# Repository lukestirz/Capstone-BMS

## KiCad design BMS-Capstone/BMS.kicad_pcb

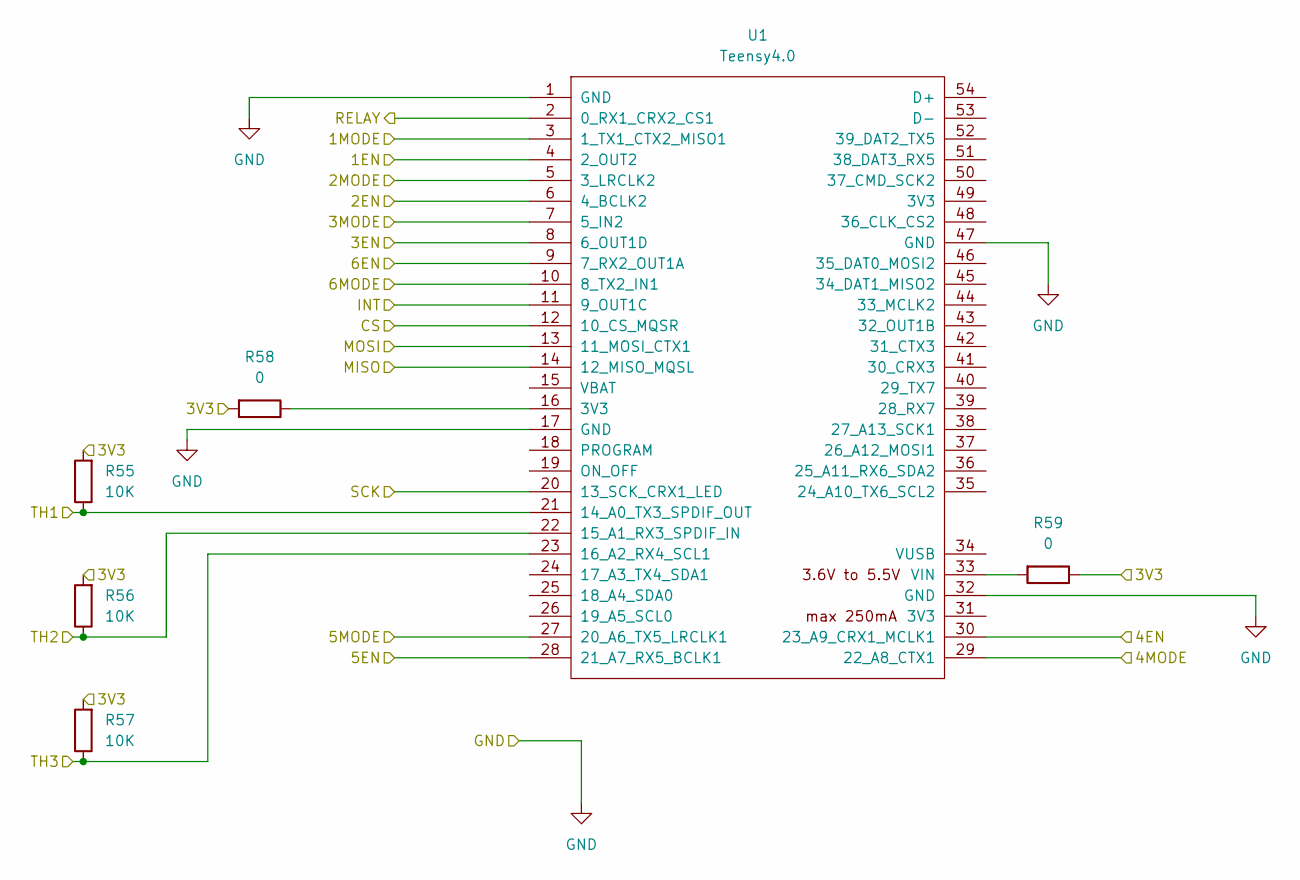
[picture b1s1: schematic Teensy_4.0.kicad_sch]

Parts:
R55, R56, R57: 10K; R_0805_2012Metric
R58, R59: 0; R_0805_2012Metric
U1: Teensy4.0; Teensy40_SMT

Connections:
/BMS Board/1EN: U1.4 (2_OUT2); also elsewhere on the board
/BMS Board/1MODE: U1.3 (1_TX1_CTX2_MISO1); also elsewhere on the board
/BMS Board/2EN: U1.6 (4_BCLK2); also elsewhere on the board
/BMS Board/2MODE: U1.5 (3_LRCLK2); also elsewhere on the board
/BMS Board/3EN: U1.8 (6_OUT1D); also elsewhere on the board
/BMS Board/3MODE: U1.7 (5_IN2); also elsewhere on the board
/BMS Board/4EN: U1.30 (23_A9_CRX1_MCLK1); also elsewhere on the board
/BMS Board/4MODE: U1.29 (22_A8_CTX1); also elsewhere on the board
/BMS Board/5EN: U1.28 (21_A7_RX5_BCLK1); also elsewhere on the board
/BMS Board/5MODE: U1.27 (20_A6_TX5_LRCLK1); also elsewhere on the board
/BMS Board/6EN: U1.9 (7_RX2_OUT1A); also elsewhere on the board
/BMS Board/6MODE: U1.10 (8_TX2_IN1); also elsewhere on the board
/BMS Board/RELAY: U1.2 (0_RX1_CRX2_CS1); also elsewhere on the board
/BMS Board/TH1: R55.1, U1.21 (14_A0_TX3_SPDIF_OUT); also elsewhere on the board
/BMS Board/TH2: R56.1, U1.22 (15_A1_RX3_SPDIF_IN); also elsewhere on the board
/BMS Board/TH3: R57.1, U1.23 (16_A2_RX4_SCL1); also elsewhere on the board
/Monitoring/3.3V: R55.2, R56.2, R57.2, R58.2, R59.1; also elsewhere on the board
/Monitoring/INT: U1.11 (9_OUT1C); also elsewhere on the board
/Monitoring/SPI_CS: U1.12 (10_CS_MQSR); also elsewhere on the board
/Monitoring/SPI_MISO: U1.14 (12_MISO_MQSL); also elsewhere on the board
/Monitoring/SPI_MOSI: U1.13 (11_MOSI_CTX1); also elsewhere on the board
/Monitoring/SPI_SCLK: U1.20 (13_SCK_CRX1_LED); also elsewhere on the board
GND: U1.1 (GND), U1.17 (GND), U1.32 (GND), U1.47 (GND); also elsewhere on the board
unnamed: R58.1, U1.16 (3V3)
unnamed: R59.2, U1.33 (VIN)

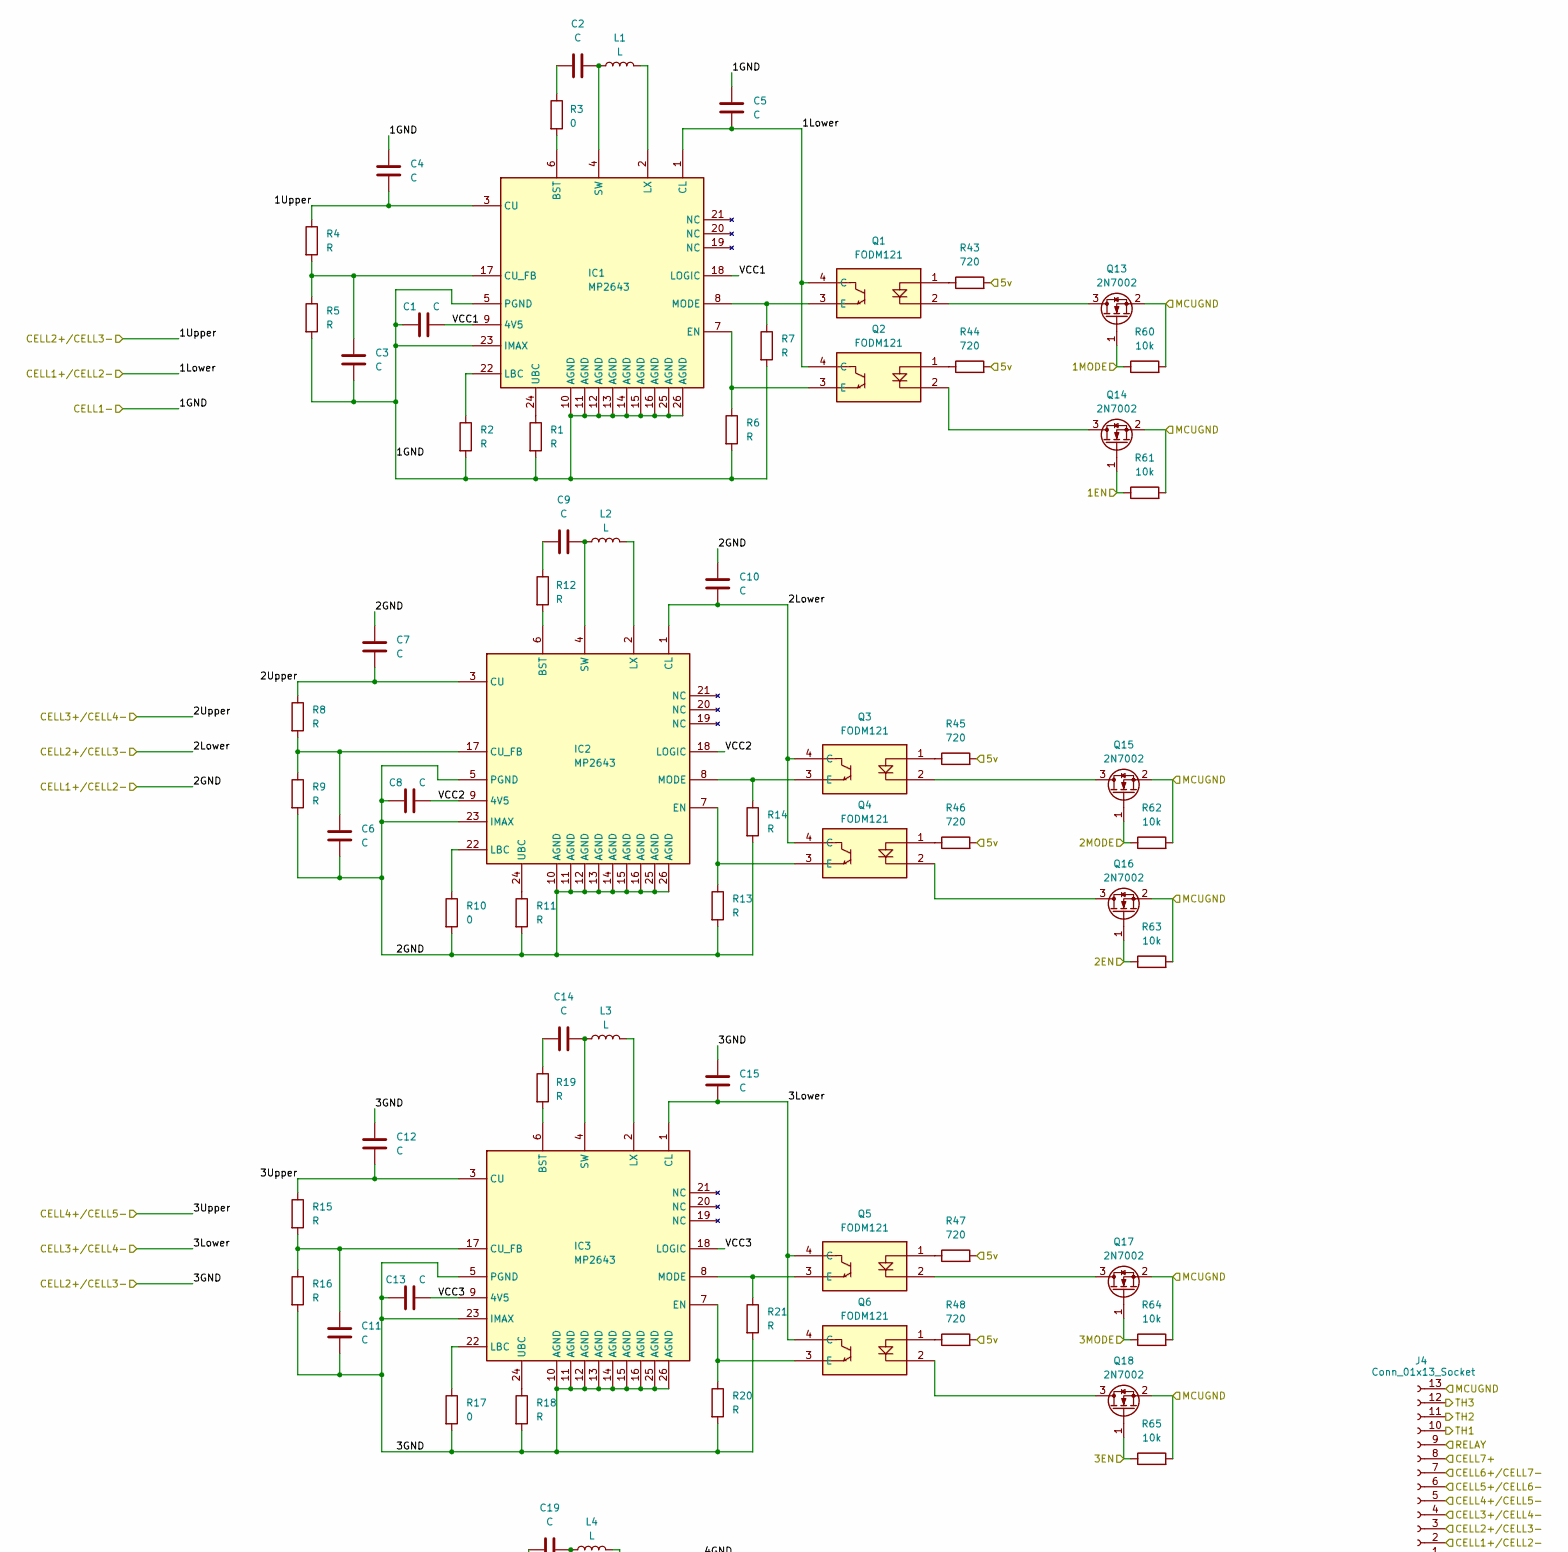
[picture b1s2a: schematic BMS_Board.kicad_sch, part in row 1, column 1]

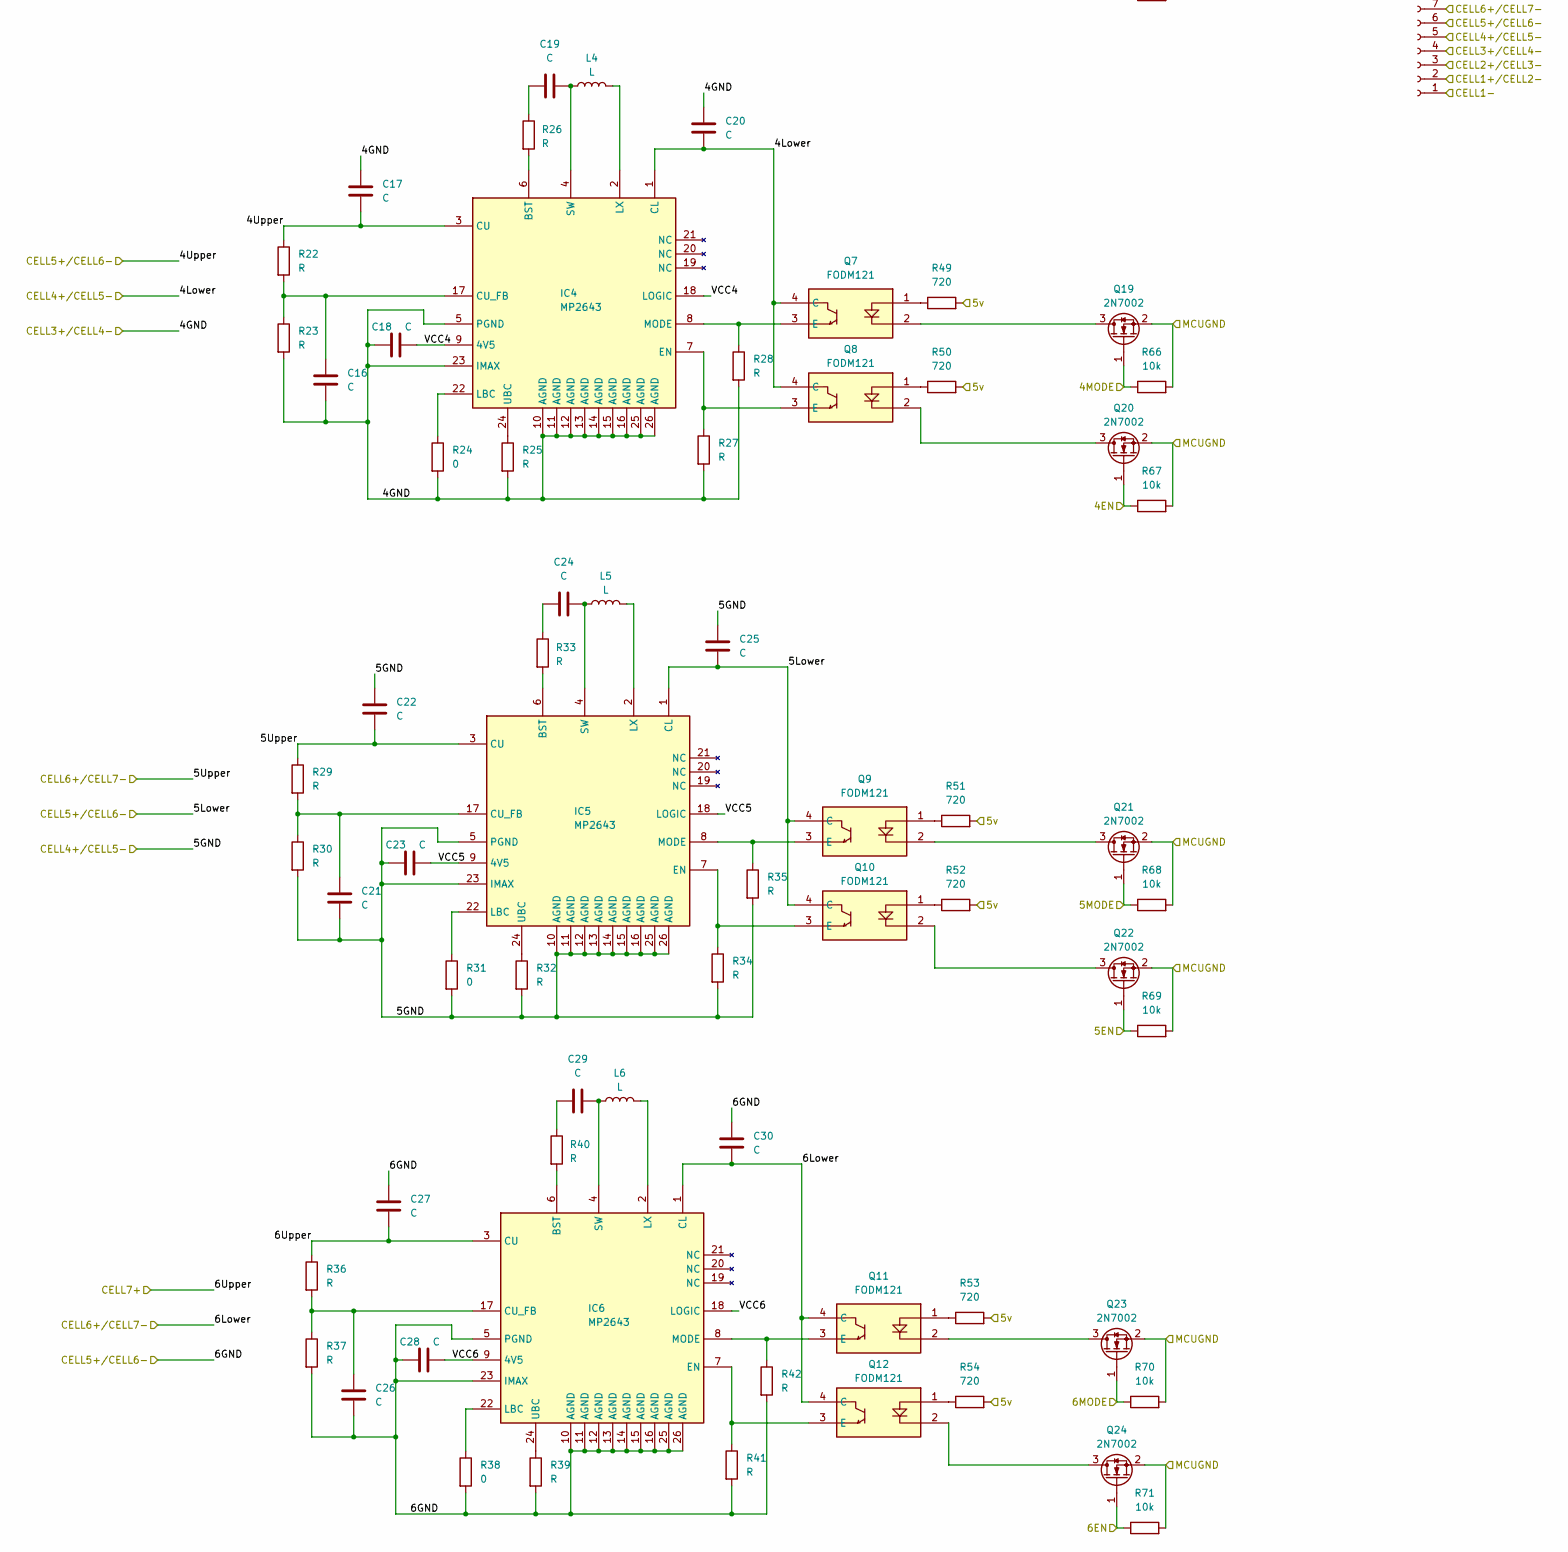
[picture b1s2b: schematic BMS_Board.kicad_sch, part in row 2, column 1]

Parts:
C1, C2, C3, C4, C5, C6, C7, C8, C9, C10, C11, C12, C13, C14, C15, C16, C17, C18, C19, C20, C21, C22, C23, C24, C25, C26, C27, C28, C29, C30: C; C_0805_2012Metric
IC1, IC2, IC3, IC4, IC5, IC6: MP2643; MP2639AGRZ; Manufacturer_Part_Number MP2639AGR-Z; Mouser Part Number 946-MP2639AGR-Z
J4: Conn_01x13_Socket; JST_XH_B13B-XH-A_1x13_P2.50mm_Vertical
L1, L2, L3, L4, L5, L6: L; MPLAL4020R47 Inductor
Q1, Q2, Q3, Q4, Q5, Q6, Q7, Q8, Q9, Q10, Q11, Q12: FODM121; SOP254P675X240-4N; Manufacturer_Part_Number FODM121; Mouser Part Number 512-FODM121
Q13, Q14, Q15, Q16, Q17, Q18, Q19, Q20, Q21, Q22, Q23, Q24: 2N7002; SOT-23
R1, R2, R4, R5, R6, R7, R8, R9, R11, R12, R13, R14, R15, R16, R18, R19, R20, R21, R22, R23, R25, R26, R27, R28, R29, R30, R32, R33, R34, R35, R36, R37, R39, R40, R41, R42: R; R_0805_2012Metric
R3, R10, R17, R24, R31, R38: 0; R_0805_2012Metric
R43, R44, R45, R46, R47, R48, R49, R50, R51, R52, R53, R54: 720; R_0805_2012Metric
R60, R61, R62, R63, R64, R65, R66, R67, R68, R69, R70, R71: 10k; R_0805_2012Metric

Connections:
/BMS Board/1EN: Q14.1 (G), R61.1; also elsewhere on the board
/BMS Board/1GND: C1.1, C3.1, C4.2, C5.2, IC1.5 (PGND), IC1.10 (AGND), IC1.11 (AGND), IC1.12 (AGND), IC1.13 (AGND), IC1.14 (AGND), IC1.15 (AGND), IC1.16 (AGND), IC1.23 (IMAX), IC1.25 (AGND), IC1.26 (AGND), J4.1, R1.2, R2.2, R5.2, R6.2, R7.2; also elsewhere on the board
/BMS Board/1Lower: C5.1, C6.1, C7.2, C8.1, C10.2, IC1.1 (CL), IC2.5 (PGND), IC2.10 (AGND), IC2.11 (AGND), IC2.12 (AGND), IC2.13 (AGND), IC2.14 (AGND), IC2.15 (AGND), IC2.16 (AGND), IC2.23 (IMAX), IC2.25 (AGND), IC2.26 (AGND), J4.2, Q1.4 (C), Q2.4 (C), R9.2, R10.2, R11.2, R13.2, R14.2; also elsewhere on the board
/BMS Board/1MODE: Q13.1 (G), R60.1; also elsewhere on the board
/BMS Board/1Upper: C4.1, C10.1, C11.1, C12.2, C13.1, C15.2, IC1.3 (CU), IC2.1 (CL), IC3.5 (PGND), IC3.10 (AGND), IC3.11 (AGND), IC3.12 (AGND), IC3.13 (AGND), IC3.14 (AGND), IC3.15 (AGND), IC3.16 (AGND), IC3.23 (IMAX), IC3.25 (AGND), IC3.26 (AGND), J4.3, Q3.4 (C), Q4.4 (C), R4.1, R16.2, R17.2, R18.2, R20.2, R21.2; also elsewhere on the board
/BMS Board/2EN: Q16.1 (G), R63.1; also elsewhere on the board
/BMS Board/2MODE: Q15.1 (G), R62.1; also elsewhere on the board
/BMS Board/2Upper: C7.1, C15.1, C16.1, C17.2, C18.1, C20.2, IC2.3 (CU), IC3.1 (CL), IC4.5 (PGND), IC4.10 (AGND), IC4.11 (AGND), IC4.12 (AGND), IC4.13 (AGND), IC4.14 (AGND), IC4.15 (AGND), IC4.16 (AGND), IC4.23 (IMAX), IC4.25 (AGND), IC4.26 (AGND), J4.4, Q5.4 (C), Q6.4 (C), R8.1, R23.2, R24.2, R25.2, R27.2, R28.2; also elsewhere on the board
/BMS Board/3EN: Q18.1 (G), R65.1; also elsewhere on the board
/BMS Board/3MODE: Q17.1 (G), R64.1; also elsewhere on the board
/BMS Board/3Upper: C12.1, C20.1, C21.1, C22.2, C23.1, C25.2, IC3.3 (CU), IC4.1 (CL), IC5.5 (PGND), IC5.10 (AGND), IC5.11 (AGND), IC5.12 (AGND), IC5.13 (AGND), IC5.14 (AGND), IC5.15 (AGND), IC5.16 (AGND), IC5.23 (IMAX), IC5.25 (AGND), IC5.26 (AGND), J4.5, Q7.4 (C), Q8.4 (C), R15.1, R30.2, R31.2, R32.2, R34.2, R35.2; also elsewhere on the board
/BMS Board/4EN: Q20.1 (G), R67.1; also elsewhere on the board
/BMS Board/4MODE: Q19.1 (G), R66.1; also elsewhere on the board
/BMS Board/4Upper: C17.1, C25.1, C26.1, C27.2, C28.1, C30.2, IC4.3 (CU), IC5.1 (CL), IC6.5 (PGND), IC6.10 (AGND), IC6.11 (AGND), IC6.12 (AGND), IC6.13 (AGND), IC6.14 (AGND), IC6.15 (AGND), IC6.16 (AGND), IC6.23 (IMAX), IC6.25 (AGND), IC6.26 (AGND), J4.6, Q9.4 (C), Q10.4 (C), R22.1, R37.2, R38.2, R39.2, R41.2, R42.2; also elsewhere on the board
/BMS Board/5EN: Q22.1 (G), R69.1; also elsewhere on the board
/BMS Board/5MODE: Q21.1 (G), R68.1; also elsewhere on the board
/BMS Board/5Upper: C22.1, C30.1, IC5.3 (CU), IC6.1 (CL), J4.7, Q11.4 (C), Q12.4 (C), R29.1; also elsewhere on the board
/BMS Board/5v: R43.2, R44.2, R45.2, R46.2, R47.2, R48.2, R49.2, R50.2, R51.2, R52.2, R53.2, R54.2; also elsewhere on the board
/BMS Board/6EN: Q24.1 (G), R71.1; also elsewhere on the board
/BMS Board/6MODE: Q23.1 (G), R70.1; also elsewhere on the board
/BMS Board/6Upper: C27.1, IC6.3 (CU), J4.8, R36.1; also elsewhere on the board
/BMS Board/RELAY: J4.9; also elsewhere on the board
/BMS Board/TH1: J4.10; also elsewhere on the board
/BMS Board/TH2: J4.11; also elsewhere on the board
/BMS Board/TH3: J4.12; also elsewhere on the board
/BMS Board/VCC1: C1.2, IC1.9 (4V5), IC1.18 (LOGIC)
/BMS Board/VCC2: C8.2, IC2.9 (4V5), IC2.18 (LOGIC)
/BMS Board/VCC3: C13.2, IC3.9 (4V5), IC3.18 (LOGIC)
/BMS Board/VCC4: C18.2, IC4.9 (4V5), IC4.18 (LOGIC)
/BMS Board/VCC5: C23.2, IC5.9 (4V5), IC5.18 (LOGIC)
/BMS Board/VCC6: C28.2, IC6.9 (4V5), IC6.18 (LOGIC)
GND: J4.13, Q13.2 (S), Q14.2 (S), Q15.2 (S), Q16.2 (S), Q17.2 (S), Q18.2 (S), Q19.2 (S), Q20.2 (S), Q21.2 (S), Q22.2 (S), Q23.2 (S), Q24.2 (S), R60.2, R61.2, R62.2, R63.2, R64.2, R65.2, R66.2, R67.2, R68.2, R69.2, R70.2, R71.2; also elsewhere on the board
unnamed: C2.1, R3.1
unnamed: C9.1, R12.1
unnamed: C14.1, R19.1
unnamed: C19.1, R26.1
unnamed: C24.1, R33.1
unnamed: C29.1, R40.1
unnamed: IC1.6 (BST), R3.2
unnamed: C3.2, IC1.17 (CU_FB), R4.2, R5.1
unnamed: IC1.7 (EN), Q2.3 (E), R6.1
unnamed: IC1.22 (LBC), R2.1
unnamed: IC1.2 (LX), L1.2
unnamed: IC1.8 (MODE), Q1.3 (E), R7.1
unnamed: C2.2, IC1.4 (SW), L1.1
unnamed: IC1.24 (UBC), R1.1
unnamed: IC2.6 (BST), R12.2
unnamed: C6.2, IC2.17 (CU_FB), R8.2, R9.1
unnamed: IC2.7 (EN), Q4.3 (E), R13.1
unnamed: IC2.22 (LBC), R10.1
unnamed: IC2.2 (LX), L2.2
unnamed: IC2.8 (MODE), Q3.3 (E), R14.1
unnamed: C9.2, IC2.4 (SW), L2.1
unnamed: IC2.24 (UBC), R11.1
unnamed: IC3.6 (BST), R19.2
unnamed: C11.2, IC3.17 (CU_FB), R15.2, R16.1
unnamed: IC3.7 (EN), Q6.3 (E), R20.1
unnamed: IC3.22 (LBC), R17.1
unnamed: IC3.2 (LX), L3.2
unnamed: IC3.8 (MODE), Q5.3 (E), R21.1
unnamed: C14.2, IC3.4 (SW), L3.1
unnamed: IC3.24 (UBC), R18.1
unnamed: IC4.6 (BST), R26.2
unnamed: C16.2, IC4.17 (CU_FB), R22.2, R23.1
unnamed: IC4.7 (EN), Q8.3 (E), R27.1
unnamed: IC4.22 (LBC), R24.1
unnamed: IC4.2 (LX), L4.2
unnamed: IC4.8 (MODE), Q7.3 (E), R28.1
unnamed: C19.2, IC4.4 (SW), L4.1
unnamed: IC4.24 (UBC), R25.1
unnamed: IC5.6 (BST), R33.2
unnamed: C21.2, IC5.17 (CU_FB), R29.2, R30.1
unnamed: IC5.7 (EN), Q10.3 (E), R34.1
unnamed: IC5.22 (LBC), R31.1
unnamed: IC5.2 (LX), L5.2
unnamed: IC5.8 (MODE), Q9.3 (E), R35.1
unnamed: C24.2, IC5.4 (SW), L5.1
unnamed: IC5.24 (UBC), R32.1
unnamed: IC6.6 (BST), R40.2
unnamed: C26.2, IC6.17 (CU_FB), R36.2, R37.1
unnamed: IC6.7 (EN), Q12.3 (E), R41.1
unnamed: IC6.22 (LBC), R38.1
unnamed: IC6.2 (LX), L6.2
unnamed: IC6.8 (MODE), Q11.3 (E), R42.1
unnamed: C29.2, IC6.4 (SW), L6.1
unnamed: IC6.24 (UBC), R39.1
unnamed: Q1.1, R43.1
unnamed: Q2.1, R44.1
unnamed: Q3.1, R45.1
unnamed: Q4.1, R46.1
unnamed: Q5.1, R47.1
unnamed: Q6.1, R48.1
unnamed: Q7.1, R49.1
unnamed: Q8.1, R50.1
unnamed: Q9.1, R51.1
unnamed: Q10.1, R52.1
unnamed: Q11.1, R53.1
unnamed: Q12.1, R54.1
unnamed: Q1.2, Q13.3 (D)
unnamed: Q2.2, Q14.3 (D)
unnamed: Q3.2, Q15.3 (D)
unnamed: Q4.2, Q16.3 (D)
unnamed: Q5.2, Q17.3 (D)
unnamed: Q6.2, Q18.3 (D)
unnamed: Q7.2, Q19.3 (D)
unnamed: Q8.2, Q20.3 (D)
unnamed: Q9.2, Q21.3 (D)
unnamed: Q10.2, Q22.3 (D)
unnamed: Q11.2, Q23.3 (D)
unnamed: Q12.2, Q24.3 (D)

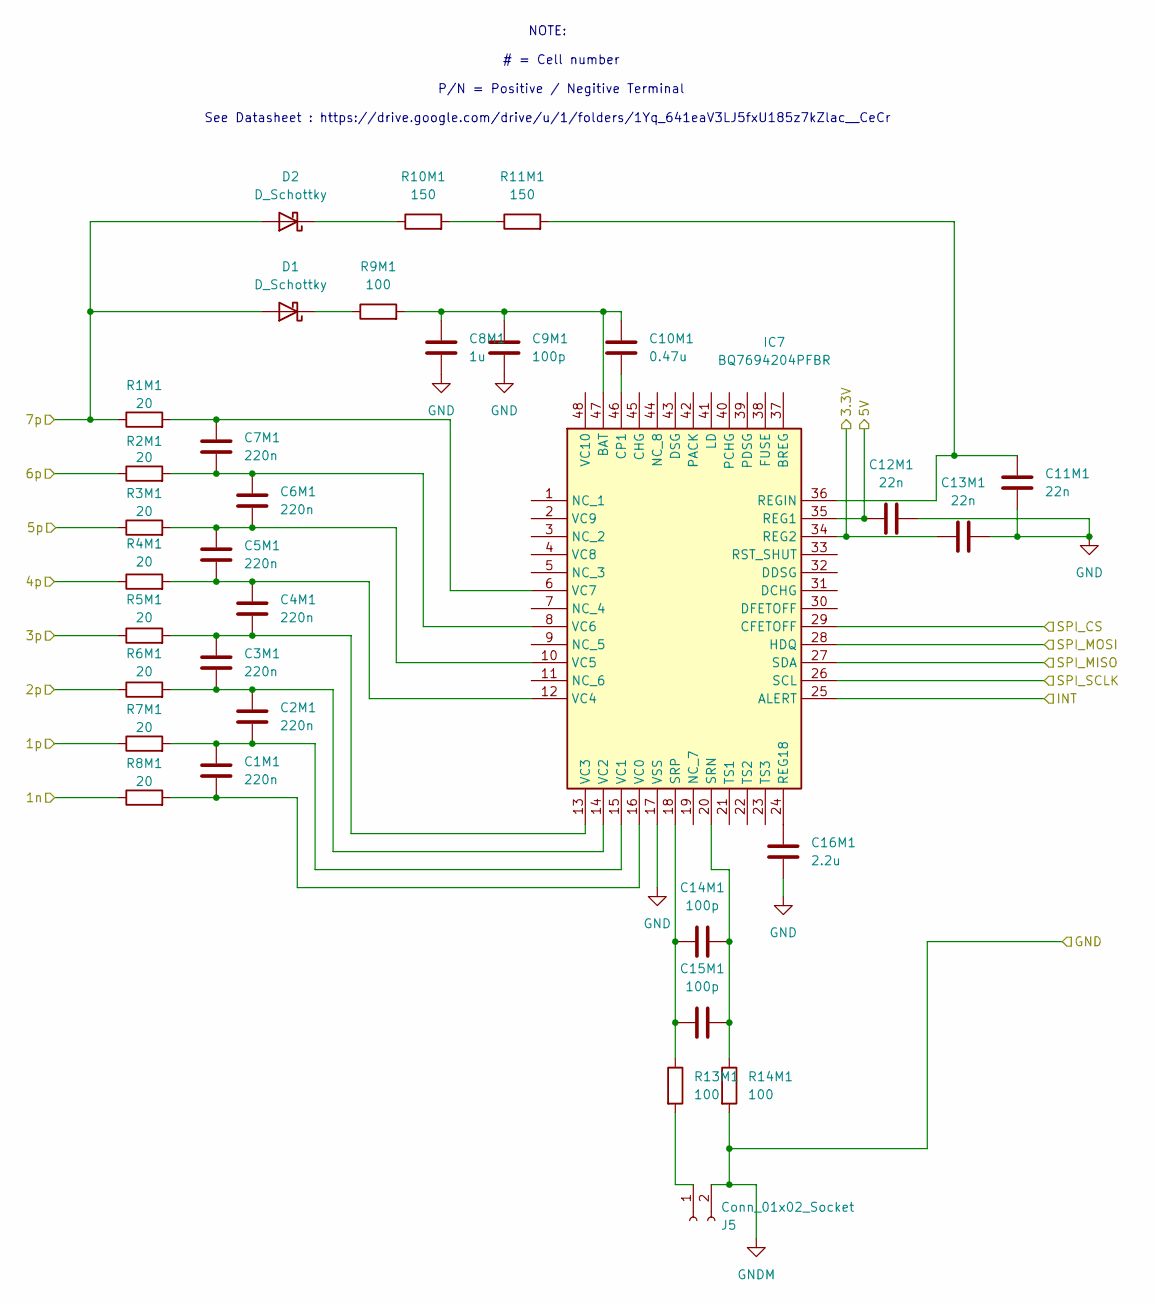
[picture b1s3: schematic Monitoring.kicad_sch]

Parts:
C1M1, C2M1, C3M1, C4M1, C5M1, C6M1, C7M1: 220n; C_0805_2012Metric
C8M1: 1u; C_0805_2012Metric
C9M1, C14M1, C15M1: 100p; C_0805_2012Metric
C10M1: 0.47u; C_0805_2012Metric
C11M1, C12M1, C13M1: 22n; C_0805_2012Metric
C16M1: 2.2u; C_0805_2012Metric
D1, D2: D_Schottky; D_0805_2012Metric
IC7: BQ7694204PFBR; Texas_PHP0048E_HTQFP-48-1EP_7x7mm_P0.5mm_EP6.5x6.5mm_Mask3.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; Manufacturer_Part_Number BQ7694204PFBR; Mouser Part Number 595-BQ7694204PFBR
J5: Conn_01x02_Socket; PinHeader_1x02_P2.54mm_Vertical
R1M1, R2M1, R3M1, R4M1, R5M1, R6M1, R7M1, R8M1: 20; R_0805_2012Metric
R9M1, R13M1, R14M1: 100; R_0805_2012Metric
R10M1, R11M1: 150; R_0805_2012Metric

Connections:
/BMS Board/1GND: R8M1.1; also elsewhere on the board
/BMS Board/1Lower: R7M1.1; also elsewhere on the board
/BMS Board/1Upper: R6M1.1; also elsewhere on the board
/BMS Board/2Upper: R5M1.1; also elsewhere on the board
/BMS Board/3Upper: R4M1.1; also elsewhere on the board
/BMS Board/4Upper: R3M1.1; also elsewhere on the board
/BMS Board/5Upper: R2M1.1; also elsewhere on the board
/BMS Board/5v: C12M1.1, IC7.35 (REG1); also elsewhere on the board
/BMS Board/6Upper: D1.2 (A), D2.2 (A), R1M1.1; also elsewhere on the board
/Monitoring/3.3V: C13M1.1, IC7.34 (REG2); also elsewhere on the board
/Monitoring/INT: IC7.25 (ALERT); also elsewhere on the board
/Monitoring/SPI_CS: IC7.29 (CFETOFF); also elsewhere on the board
/Monitoring/SPI_MISO: IC7.27 (SDA); also elsewhere on the board
/Monitoring/SPI_MOSI: IC7.28 (HDQ); also elsewhere on the board
/Monitoring/SPI_SCLK: IC7.26 (SCL); also elsewhere on the board
GND: C8M1.2, C9M1.2, C11M1.2, C12M1.2, C13M1.2, C16M1.2, IC7.17 (VSS), J5.2, R14M1.2; also elsewhere on the board
unnamed: D1.1 (K), R9M1.1
unnamed: D2.1 (K), R10M1.1
unnamed: C8M1.1, C9M1.1, C10M1.1, IC7.47 (BAT), R9M1.2
unnamed: C10M1.2, IC7.46 (CP1)
unnamed: C16M1.1, IC7.24 (REG18)
unnamed: C11M1.1, IC7.36 (REGIN), R11M1.2
unnamed: C14M1.1, C15M1.1, IC7.20 (SRN), R14M1.1
unnamed: C14M1.2, C15M1.2, IC7.18 (SRP), R13M1.1
unnamed: C1M1.2, IC7.16 (VC0), R8M1.2
unnamed: C1M1.1, C2M1.2, IC7.15 (VC1), R7M1.2
unnamed: C2M1.1, C3M1.2, IC7.14 (VC2), R6M1.2
unnamed: C3M1.1, C4M1.2, IC7.13 (VC3), R5M1.2
unnamed: C4M1.1, C5M1.2, IC7.12 (VC4), R4M1.2
unnamed: C5M1.1, C6M1.2, IC7.10 (VC5), R3M1.2
unnamed: C6M1.1, C7M1.2, IC7.8 (VC6), R2M1.2
unnamed: C7M1.1, IC7.6 (VC7), R1M1.2
unnamed: J5.1, R13M1.2
unnamed: R10M1.2, R11M1.1

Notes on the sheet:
NOTE: # = Cell number P/N = Positive / Negitive Terminal See Datasheet : https://drive.google.com/drive/u/1/folders/1Yq_641eaV3LJ5fxU185z7kZlac__CeCr

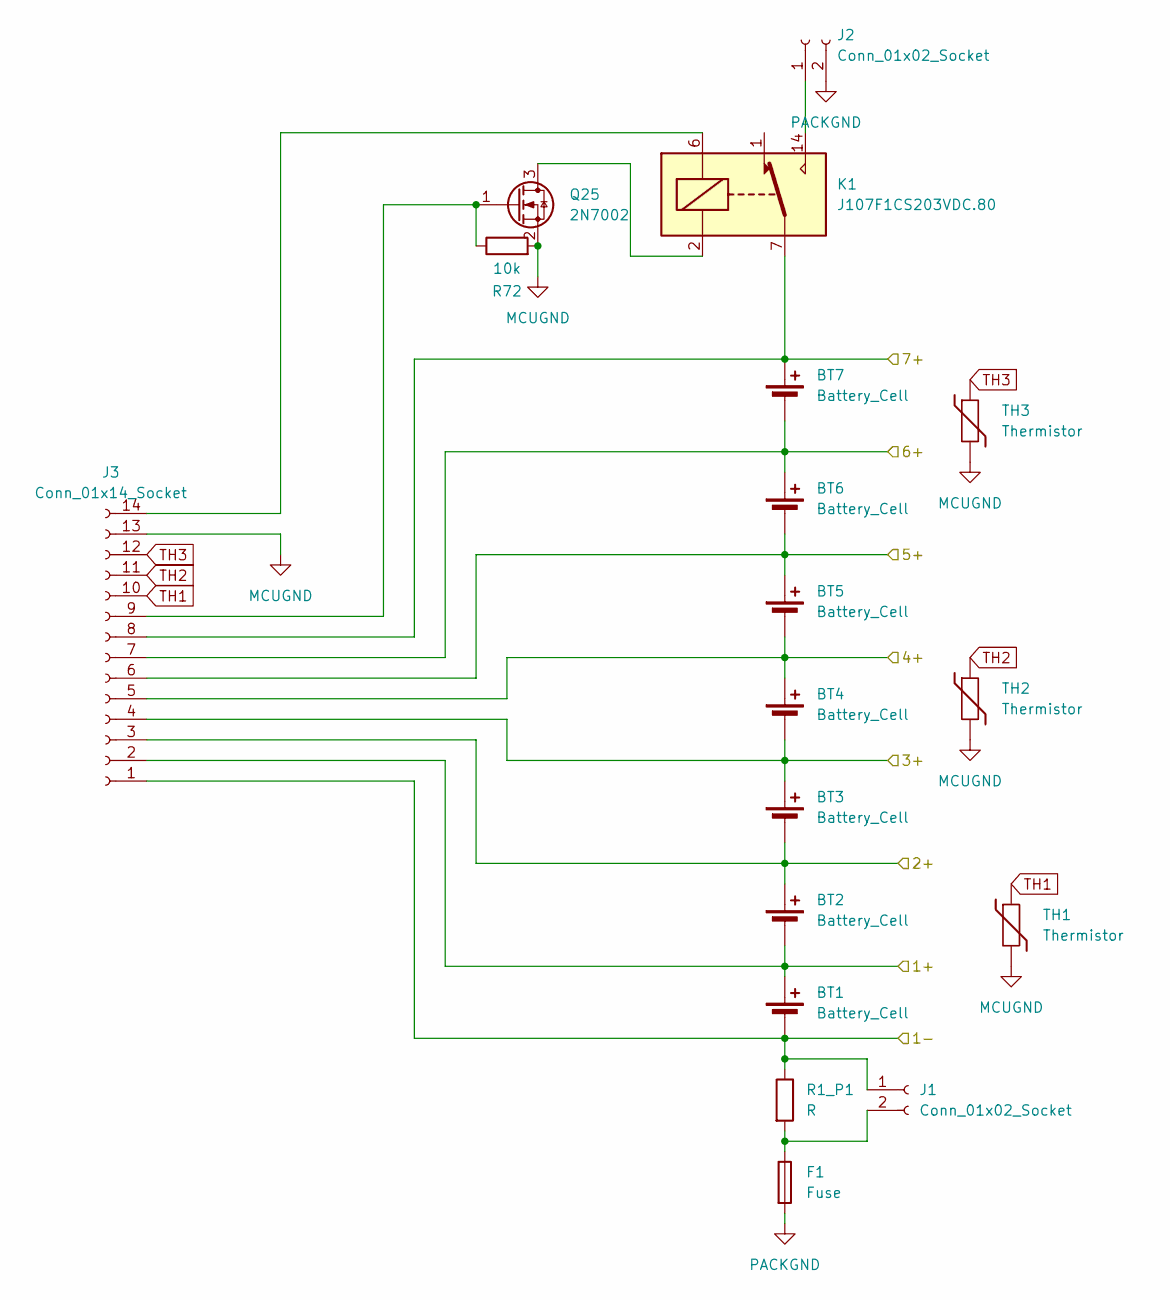
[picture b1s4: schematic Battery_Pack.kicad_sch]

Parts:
BT1, BT2, BT3, BT4, BT5, BT6, BT7: Battery_Cell; keystone 254 18650
F1: Fuse; Fuseholder_Blade_Mini_Keystone_3568
J1: Conn_01x02_Socket; PinHeader_1x02_P2.54mm_Vertical
J2: Conn_01x02_Socket; XT60
J3: Conn_01x14_Socket; JST_XH_S14B-XH-A-1_1x14_P2.50mm_Horizontal
K1: J107F1CS203VDC.80; 3_3v relay
Q25: 2N7002; SOT-23
R1_P1: R; R_1210_3225Metric
R72: 10k; R_0805_2012Metric
TH1, TH2, TH3: Thermistor; R_Axial_DIN0204_L3.6mm_D1.6mm_P2.54mm_Vertical

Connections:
/Battery Pack/1+: BT1.1 (+), BT2.2 (-), J3.2
/Battery Pack/1-: BT1.2 (-), J1.1, J3.1, R1_P1.1
/Battery Pack/2+: BT2.1 (+), BT3.2 (-), J3.3
/Battery Pack/3+: BT3.1 (+), BT4.2 (-), J3.4
/Battery Pack/4+: BT4.1 (+), BT5.2 (-), J3.5
/Battery Pack/5+: BT5.1 (+), BT6.2 (-), J3.6
/Battery Pack/6+: BT6.1 (+), BT7.2 (-), J3.7
/Battery Pack/7+: BT7.1 (+), J3.8, K1.7, K1.8
MCUGND: J3.13, Q25.2 (S), R72.2, TH1.2, TH2.2, TH3.2
unnamed: F1.1, J1.2, R1_P1.2
unnamed: J2.1, K1.14
unnamed: J3.9, Q25.1 (G), R72.1
unnamed: J3.14, K1.6
unnamed: K1.2, Q25.3 (D)
PACKGND: F1.2, J2.2
TH1: J3.10, TH1.1
TH2: J3.11, TH2.1
TH3: J3.12, TH3.1

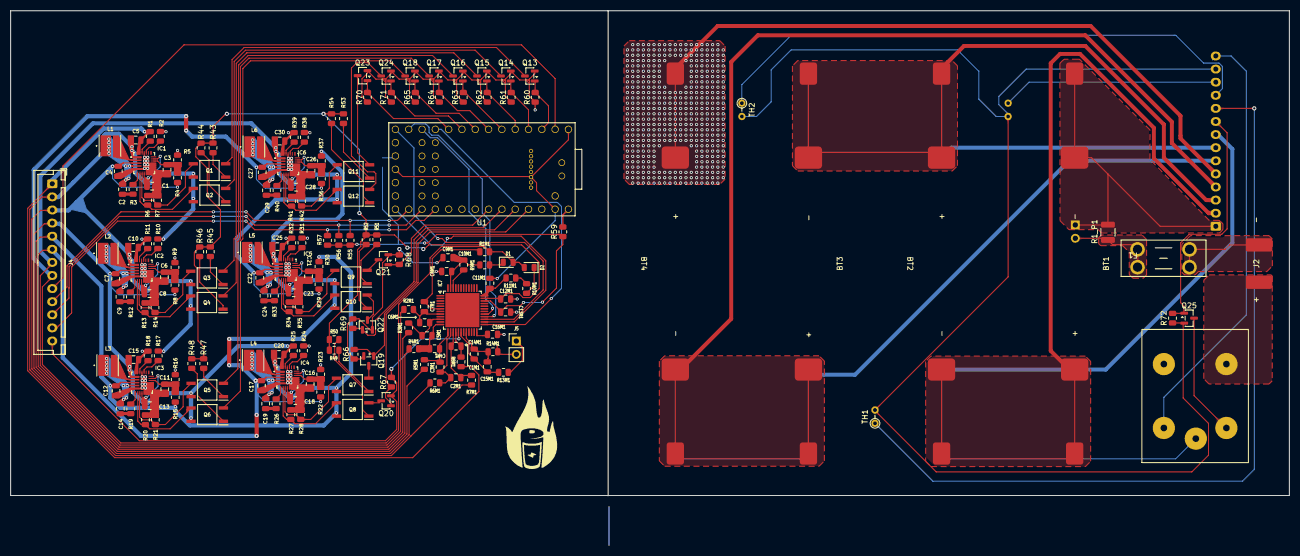
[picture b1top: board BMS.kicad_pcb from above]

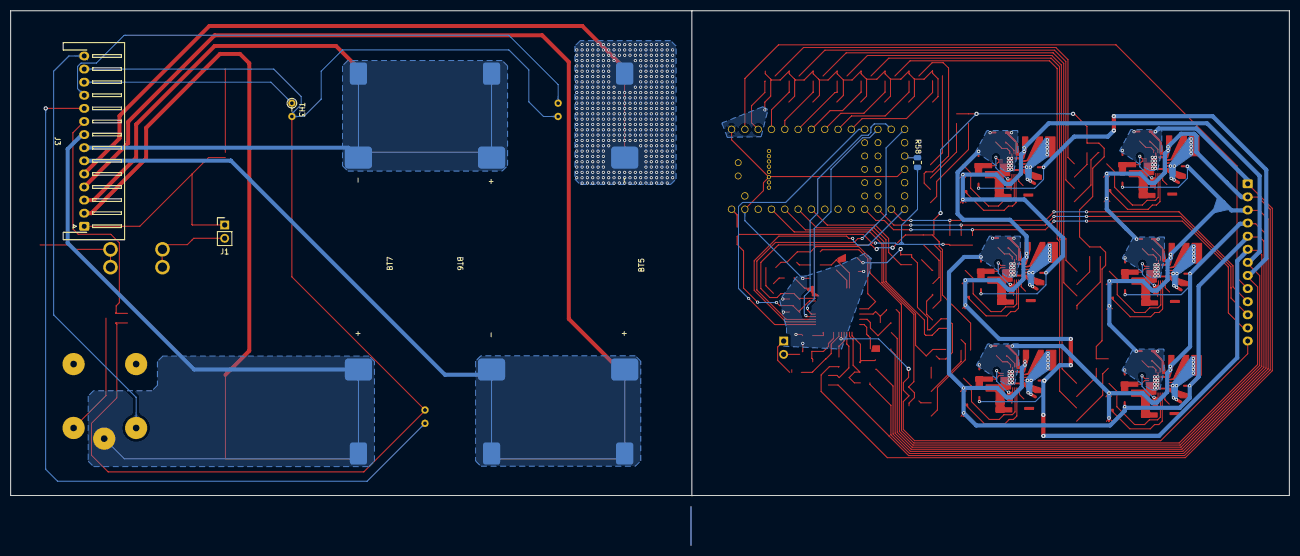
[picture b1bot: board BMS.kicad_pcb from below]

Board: 2 copper layers, 243.9 x 102.0 mm, 190 parts (7 on the bottom side), 154 nets.

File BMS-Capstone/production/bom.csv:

Designator,Footprint,Quantity,Value,LCSC Part #
"BT1, BT2, BT3, BT4, BT5, BT6, BT7",keystone 254 18650,7,Battery_Cell,
"C1, C10, C11, C12, C13, C14, C15, C16, C17, C18, C19, C2, C20, C21, C22, C23, C24, C25, C26, C27, C28, C29, C3, C30, C4, C5, C6, C7, C8, C9",0805,30,C,
C10M1,0805,1,0.47u,
"C11M1, C12M1, C13M1",0805,3,22n,
"C14M1, C15M1, C9M1",0805,3,100p,
C16M1,0805,1,2.2u,
"C1M1, C2M1, C3M1, C4M1, C5M1, C6M1, C7M1",0805,7,220n,
C8M1,0805,1,1u,
"D1, D2",0805,2,D_Schottky,
F1,Fuseholder_Blade_Mini_Keystone_3568,1,Fuse,
"IC1, IC2, IC3, IC4, IC5, IC6",MP2639AGRZ,6,MP2643,
IC7,Texas_PHP0048E_HTQFP-48-1EP_7x7mm_P0.5mm_EP6.5x6.5mm_Mask3.62x3.62mm,1,BQ7694204PFBR,
"J1, J5",PinHeader_1x02_P2.54mm_Vertical,2,Conn_01x02_Socket,
J2,XT60,1,Conn_01x02_Socket,
J3,JST_XH_S14B-XH-A-1_1x14_P2.50mm_Horizontal,1,Conn_01x14_Socket,
J4,JST_XH_B13B-XH-A_1x13_P2.50mm_Vertical,1,Conn_01x13_Socket,
K1,3_3v relay,1,J107F1CS203VDC.80,
"L1, L2, L3, L4, L5, L6",MPLAL4020R47 Inductor,6,L,
"Q1, Q10, Q11, Q12, Q2, Q3, Q4, Q5, Q6, Q7, Q8, Q9",SOP254P675X240-4N,12,FODM121,
"Q13, Q14, Q15, Q16, Q17, Q18, Q19, Q20, Q21, Q22, Q23, Q24, Q25",SOT-23,13,2N7002,
"R1, R11, R12, R13, R14, R15, R16, R18, R19, R2, R20, R21, R22, R23, R25, R26, R27, R28, R29, R30, R32, R33, R34, R35, R36, R37, R39, R4, R40, R41, R42, R5, R6, R7, R8, R9",0805,36,R,
"R10, R17, R24, R3, R31, R38, R58, R59",0805,8,0,
"R10M1, R11M1",0805,2,150,
"R13M1, R14M1, R9M1",0805,3,100,
"R1M1, R2M1, R3M1, R4M1, R5M1, R6M1, R7M1, R8M1",0805,8,20,
R1_P1,1210,1,R,
"R43, R44, R45, R46, R47, R48, R49, R50, R51, R52, R53, R54",0805,12,720,
"R55, R56, R57, R60, R61, R62, R63, R64, R65, R66, R67, R68, R69, R70, R71, R72",0805,16,10K,
"TH1, TH2, TH3",R_Axial_DIN0204_L3.6mm_D1.6mm_P2.54mm_Vertical,3,Thermistor,
U1,Teensy40_SMT,1,Teensy4.0,

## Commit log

2025-11-11 Test
2025-11-11 added branches. Each Person work on a file related to the branch name
2025-11-11 teensy branch
2025-11-12 Interfacing first commit
2025-11-12 removed test file
2025-11-12 Added Interfacing
2025-11-12 Fixing this fucking repo
2025-11-14 added resistor
2025-11-14 added hierarchial sheet for BMS[A
2025-11-14 Added MP chip
2025-11-14 Added bq chip
2025-11-14 Added symbol and footprint for MP
2025-11-14 Added cells
2025-11-14 Created Schematic for MP chip
2025-11-14 Added BQ7694204PFBR
2025-11-14 if this shit brakes our stuff im going to be pissed
2025-11-14 Added PCB Design
2025-11-14 Designed one entire MP chip layout
2025-11-15 Fixes
2025-11-15 More fixes
2025-11-15 idek
2025-11-17 added CL capacitor
2025-11-18 Ketchup
2025-11-19 Routed Cell Board
2025-11-20 Adjusted cell clip footprint
2025-11-20 added PCB shit
2025-11-20 adding more shit to this stupid project
2025-11-20 im stupid
2025-11-20 still going
2025-11-21 added Monitoring PCB
2025-11-21 did a thing
2025-11-21 crossing fingers and toes
2025-11-21 Redid the whole thing
2025-11-21 added monitoring
2025-11-21 Added fuse
2025-11-21 closed kicad
2025-11-21 Finished teensy
2025-11-21 Slight modifications
2025-11-21 added shit
2025-11-21 Current Sense Resistor
2025-11-23 I hope I didnt break anything
2025-11-24 This repo is breaking
2025-11-24 Added Teensy
2025-11-24 Added Monitoring to kicad schematic
2025-11-24 Moved PCB file to Battery_Pack_PCB branch
2025-11-24 Added Battery_Pack_PCB
2025-11-24 Added Teensy PCB
2025-11-24 Added 4 balancing boards
2025-11-24 Added all schematics to main. I was too scared to merge
2025-11-24 Added main Schematic to branch and linked components to PCB
2025-11-25 uploaded part library
2025-11-29 Copied balancer circuit onto pcb
2025-11-29 Appended the BMS board pcb
2025-11-29 Added connector to balancing schematic
2025-11-29 relinked footprints
2025-12-01 Went back to previous push
2025-12-01 Changed designators for BMS board
2025-12-01 Fixed designators for TI
2025-12-01 routing for TI chip
2025-12-02 Integrated in Monitoring board into final pcb
2025-12-02 Edge Cuts
2025-12-02 Final touches
2025-12-02 Edge cut adjustment
2025-12-02 Added V-CUT label
2025-12-03 Added Transistors for optocouple and relay drive
2025-12-03 Fixed up edge cuts and other DRC
2025-12-03 Fixed up edge cuts and other DRC part 2
2025-12-03 Changed v cut and some small corrections
2025-12-03 cool logo :)
2025-12-03 Changed back to 2 layers
2025-12-04 Final
2025-12-05 Generated BOM
